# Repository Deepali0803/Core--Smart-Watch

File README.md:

# Core--Smart-Watch
This is a design of development board for SmartWatch, designed in Eagle Autodesk with SMD and through-hole components.
It is capable of performing some basic functions such as digital read/write, analog signals, I2C and UART communications, with Bluetooth connection, RTC(real-time clock), and OLED display to set alarm and operate easily.

The power consumption in sleep mode is very low, around 1.3mA so the battery could last 2 days.

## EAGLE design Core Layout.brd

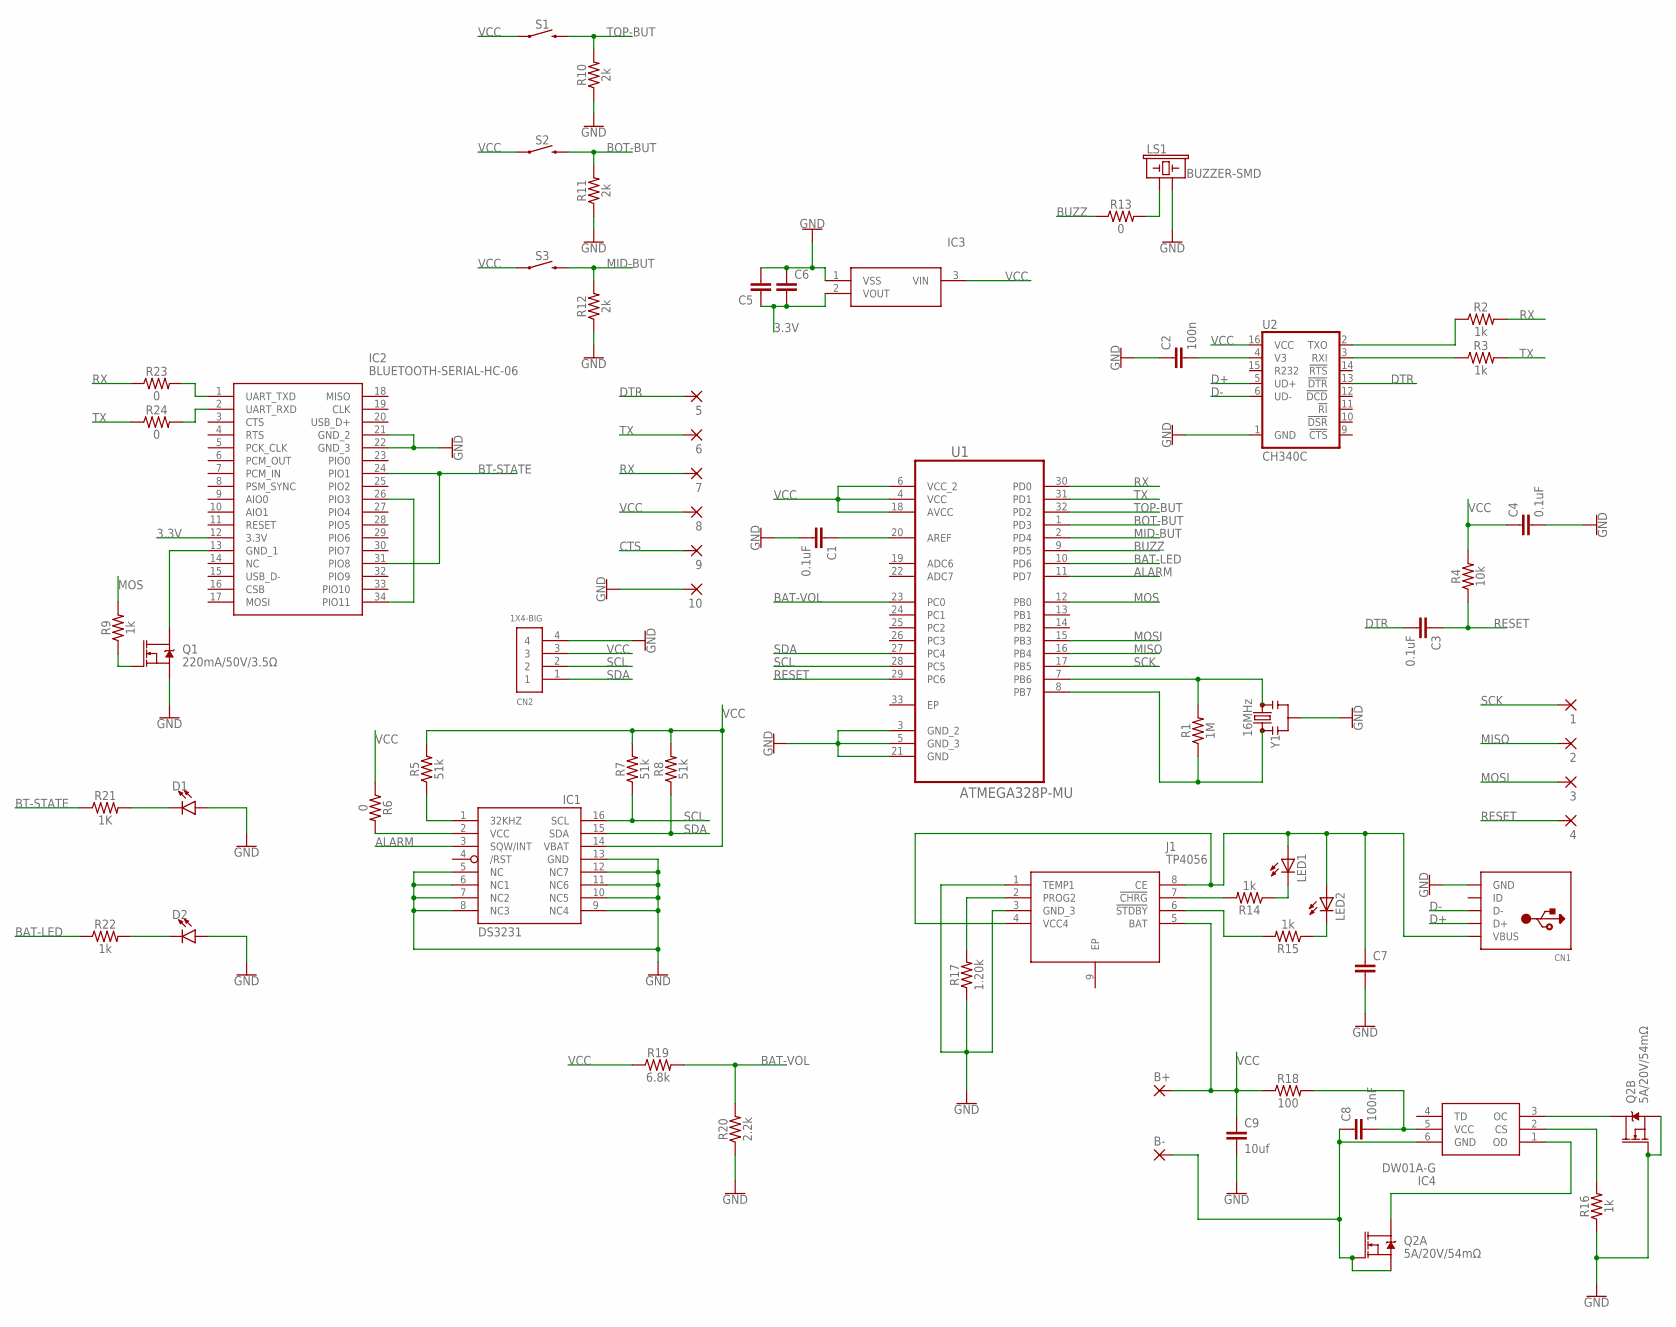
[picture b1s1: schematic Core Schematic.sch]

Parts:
1, 2, 3, 4, 5, 6, 7, 8, 9, 10: SMD2; SMD1,27-2,54
B+: SMD2; SMD1,27-2,54
B-: SMD2; SMD1,27-2,54
C1, C3, C4: 0.1uF; 0603
C2: 100n; 0603
C5, C6, C7: 4.7PF-0603-50V-5%; 0603
C8: 100nF; 0603
C9: 10uf; 0603
CN1: USBMINIB; USB-MINIB
CN2: 1X4-BIG; 1X04-BIG
D1, D2: LED0603; LED-0603
IC1: DS3231/SO; SO16W
IC2: BLUETOOTH-SERIAL-HC-06; BLUETOOTHSERIALHC06
IC3: XC6206P332MR; SOT95P280X130-3N
IC4: DW01A-G; SOT95P280X135-6N
J1: TP4056; SOIC127P600X175-9N
LED1, LED2: LEDCHIPLED_0805; CHIPLED_0805
LS1: BUZZER-SMD; BUZZER-CCV
Q1: 220mA/50V/3.5Ω; SOT23-3
Q2: 5A/20V/54mΩ; MICROFET_2X2
R1: 1M; 0603
R2, R3, R9, R14, R15, R16, R22: 1k; 0603
R4: 10k; 0603
R5, R7, R8: 51k; 0603
R6, R13, R23, R24: 0; 0603
R10, R11, R12: 2k; 0603
R17: 1.20k; 0603
R18: 100; 0603
R19: 6.8k; 0603
R20: 2.2k; 0603
R21: 1K; 0603
S1, S2, S3: MOMENTARY-SWITCH-SPST-SMD-6.0X3.5MM; TACTILE_SWITCH_SMD_6.0X3.5MM
U1: ATMEGA328P-MU; QFN50P500X500X100-33N
U2: CH340C; SO016
Y1: 16MHz; RESONATOR-SMD-3.2X1.3

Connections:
3.3V: C5.1, C6.2, IC2.12 (3.3V), IC3.2 (VOUT)
ALARM: IC1.3 (SQW/INT), U1.11 (PD7)
BAT-LED: R22.1, U1.10 (PD6)
BAT-VOL: R19.2, R20.2, U1.23 (PC0)
BOT-BUT: R11.2, S2.2, U1.1 (PD3)
BT-STATE: IC2.24 (PIO1), IC2.31 (PIO8), R21.1
BUZZ: R13.1, U1.9 (PD5)
CTS: 9.1
D+: CN1.D+, U2.5 (UD+)
D-: CN1.D-, U2.6 (UD-)
DTR: 5.1, C3.2, U2.13 (!DTR)
GND: 10.1, C1.2, C2.1, C4.2, C5.2, C6.1, C7.2, C9.2, CN1.GND, CN2.4, D1.A, D2.A, IC1.5 (NC), IC1.6 (NC1), IC1.7 (NC2), IC1.8 (NC3), IC1.9 (NC4), IC1.10 (NC5), IC1.11 (NC6), IC1.12 (NC7), IC1.13 (GND), IC2.21 (GND_2), IC2.22 (GND_3), IC3.1 (VSS), J1.1 (TEMP1), J1.3 (GND_3), LS1.- (2), Q1.2 (S), Q2.G2 (G), Q2.S2 (S), R10.1, R11.1, R12.1, R16.1, R17.1, R20.1, U1.3 (GND_2), U1.5 (GND_3), U1.21 (GND), U2.1 (GND), Y1.2
MID-BUT: R12.2, S3.2, U1.2 (PD4)
MISO: 2.1, U1.16 (PB4)
MOS: R9.2, U1.12 (PB0)
MOSI: 3.1, U1.15 (PB3)
unnamed: C1.1, U1.20 (AREF)
unnamed: IC1.1 (32KHZ), R5.1
unnamed: R1.2, U1.7 (PB6), Y1.3
unnamed: R1.1, U1.8 (PB7), Y1.1
unnamed: IC1.2 (VCC), R6.2
unnamed: IC2.13 (GND_1), Q1.3 (D)
unnamed: C2.2, U2.4 (V3)
unnamed: R3.1, U2.3 (RXI)
unnamed: Q1.1 (G), R9.1
unnamed: LS1.+ (1), R13.2
unnamed: R2.1, U2.2 (TXO)
unnamed: J1.6 (!STDBY), R15.2
unnamed: LED2.C, R15.1
unnamed: J1.7 (!CHRG), R14.2
unnamed: LED1.C, R14.1
unnamed: C7.1, CN1.VBUS, J1.4 (VCC4), J1.8 (CE), LED1.A, LED2.A
unnamed: C8.2, IC4.5 (VCC), R18.2
unnamed: B-.1, C8.1, IC4.6 (GND), Q2.G1 (G), Q2.S1 (S)
unnamed: J1.2 (PROG2), R17.2
unnamed: D2.C, R22.2
unnamed: D1.C, R21.2
unnamed: IC2.26 (PIO3), IC2.34 (PIO11)
unnamed: IC4.3 (OC), Q2.D2 (D), Q2.D2_2 (D)
unnamed: IC4.2 (CS), R16.2
unnamed: IC2.1 (UART_TXD), R23.2
unnamed: IC4.1 (OD), Q2.D1 (D), Q2.D1_2 (D)
unnamed: IC2.2 (UART_RXD), R24.2
RESET: 4.1, C3.1, R4.1, U1.29 (PC6)
RX: 7.1, R2.2, R23.1, U1.30 (PD0)
SCK: 1.1, U1.17 (PB5)
SCL: CN2.2, IC1.16 (SCL), R7.1, U1.28 (PC5)
SDA: CN2.1, IC1.15 (SDA), R8.1, U1.27 (PC4)
TOP-BUT: R10.2, S1.2, U1.32 (PD2)
TX: 6.1, R3.2, R24.1, U1.31 (PD1)
VCC: 8.1, B+.1, C4.1, C9.1, CN2.3, IC1.14 (VBAT), IC3.3 (VIN), J1.5 (BAT), R4.2, R5.2, R6.1, R7.2, R8.2, R18.1, R19.1, S1.1, S2.1, S3.1, U1.4 (VCC), U1.6 (VCC_2), U1.18 (AVCC), U2.16 (VCC)

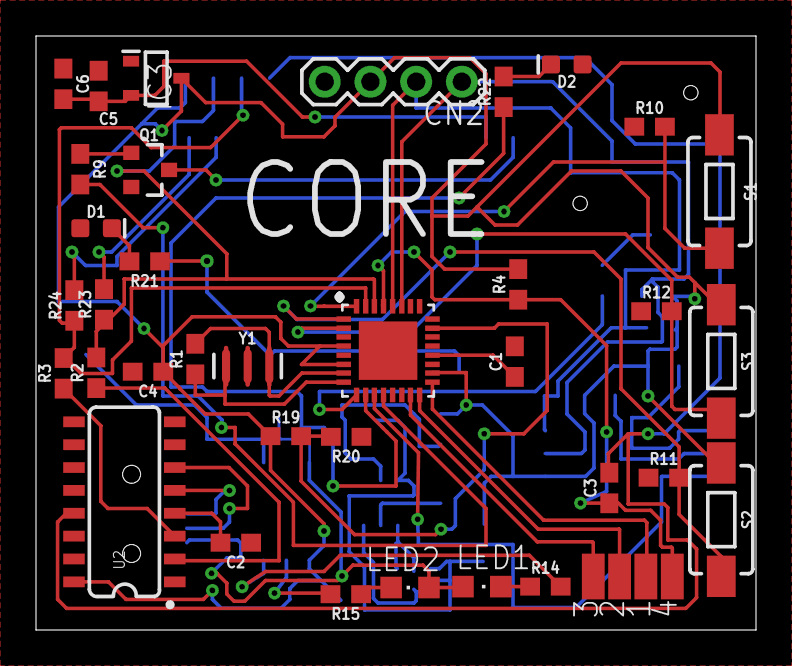
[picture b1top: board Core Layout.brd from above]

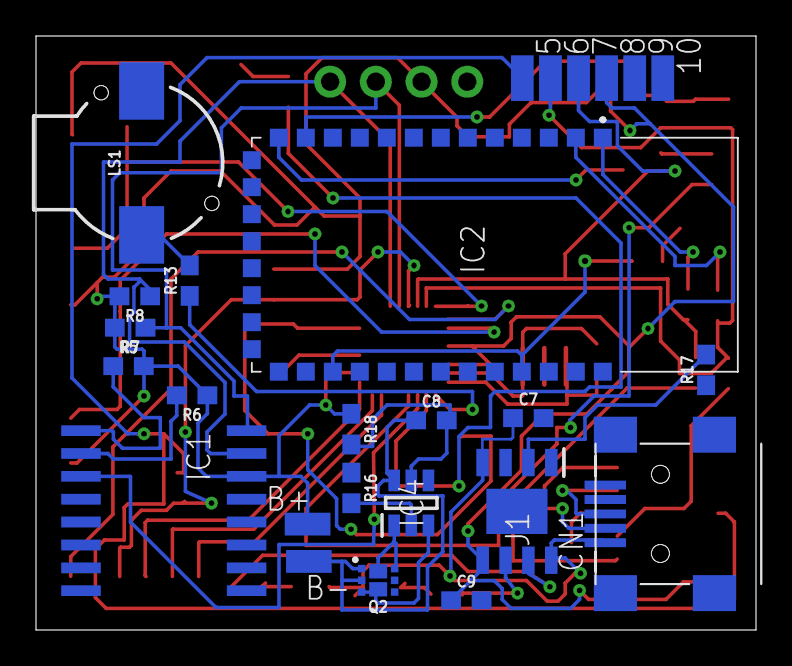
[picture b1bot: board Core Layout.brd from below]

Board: 2 copper layers, 40.0 x 33.0 mm, 65 parts (26 on the bottom side), 50 nets.

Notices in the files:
parts and their libraries:
SparkFun-Capacitors: Licensing: Creative Commons ShareAlike 4.0 International - https://creativecommons.org/licenses/by-sa/4.0
